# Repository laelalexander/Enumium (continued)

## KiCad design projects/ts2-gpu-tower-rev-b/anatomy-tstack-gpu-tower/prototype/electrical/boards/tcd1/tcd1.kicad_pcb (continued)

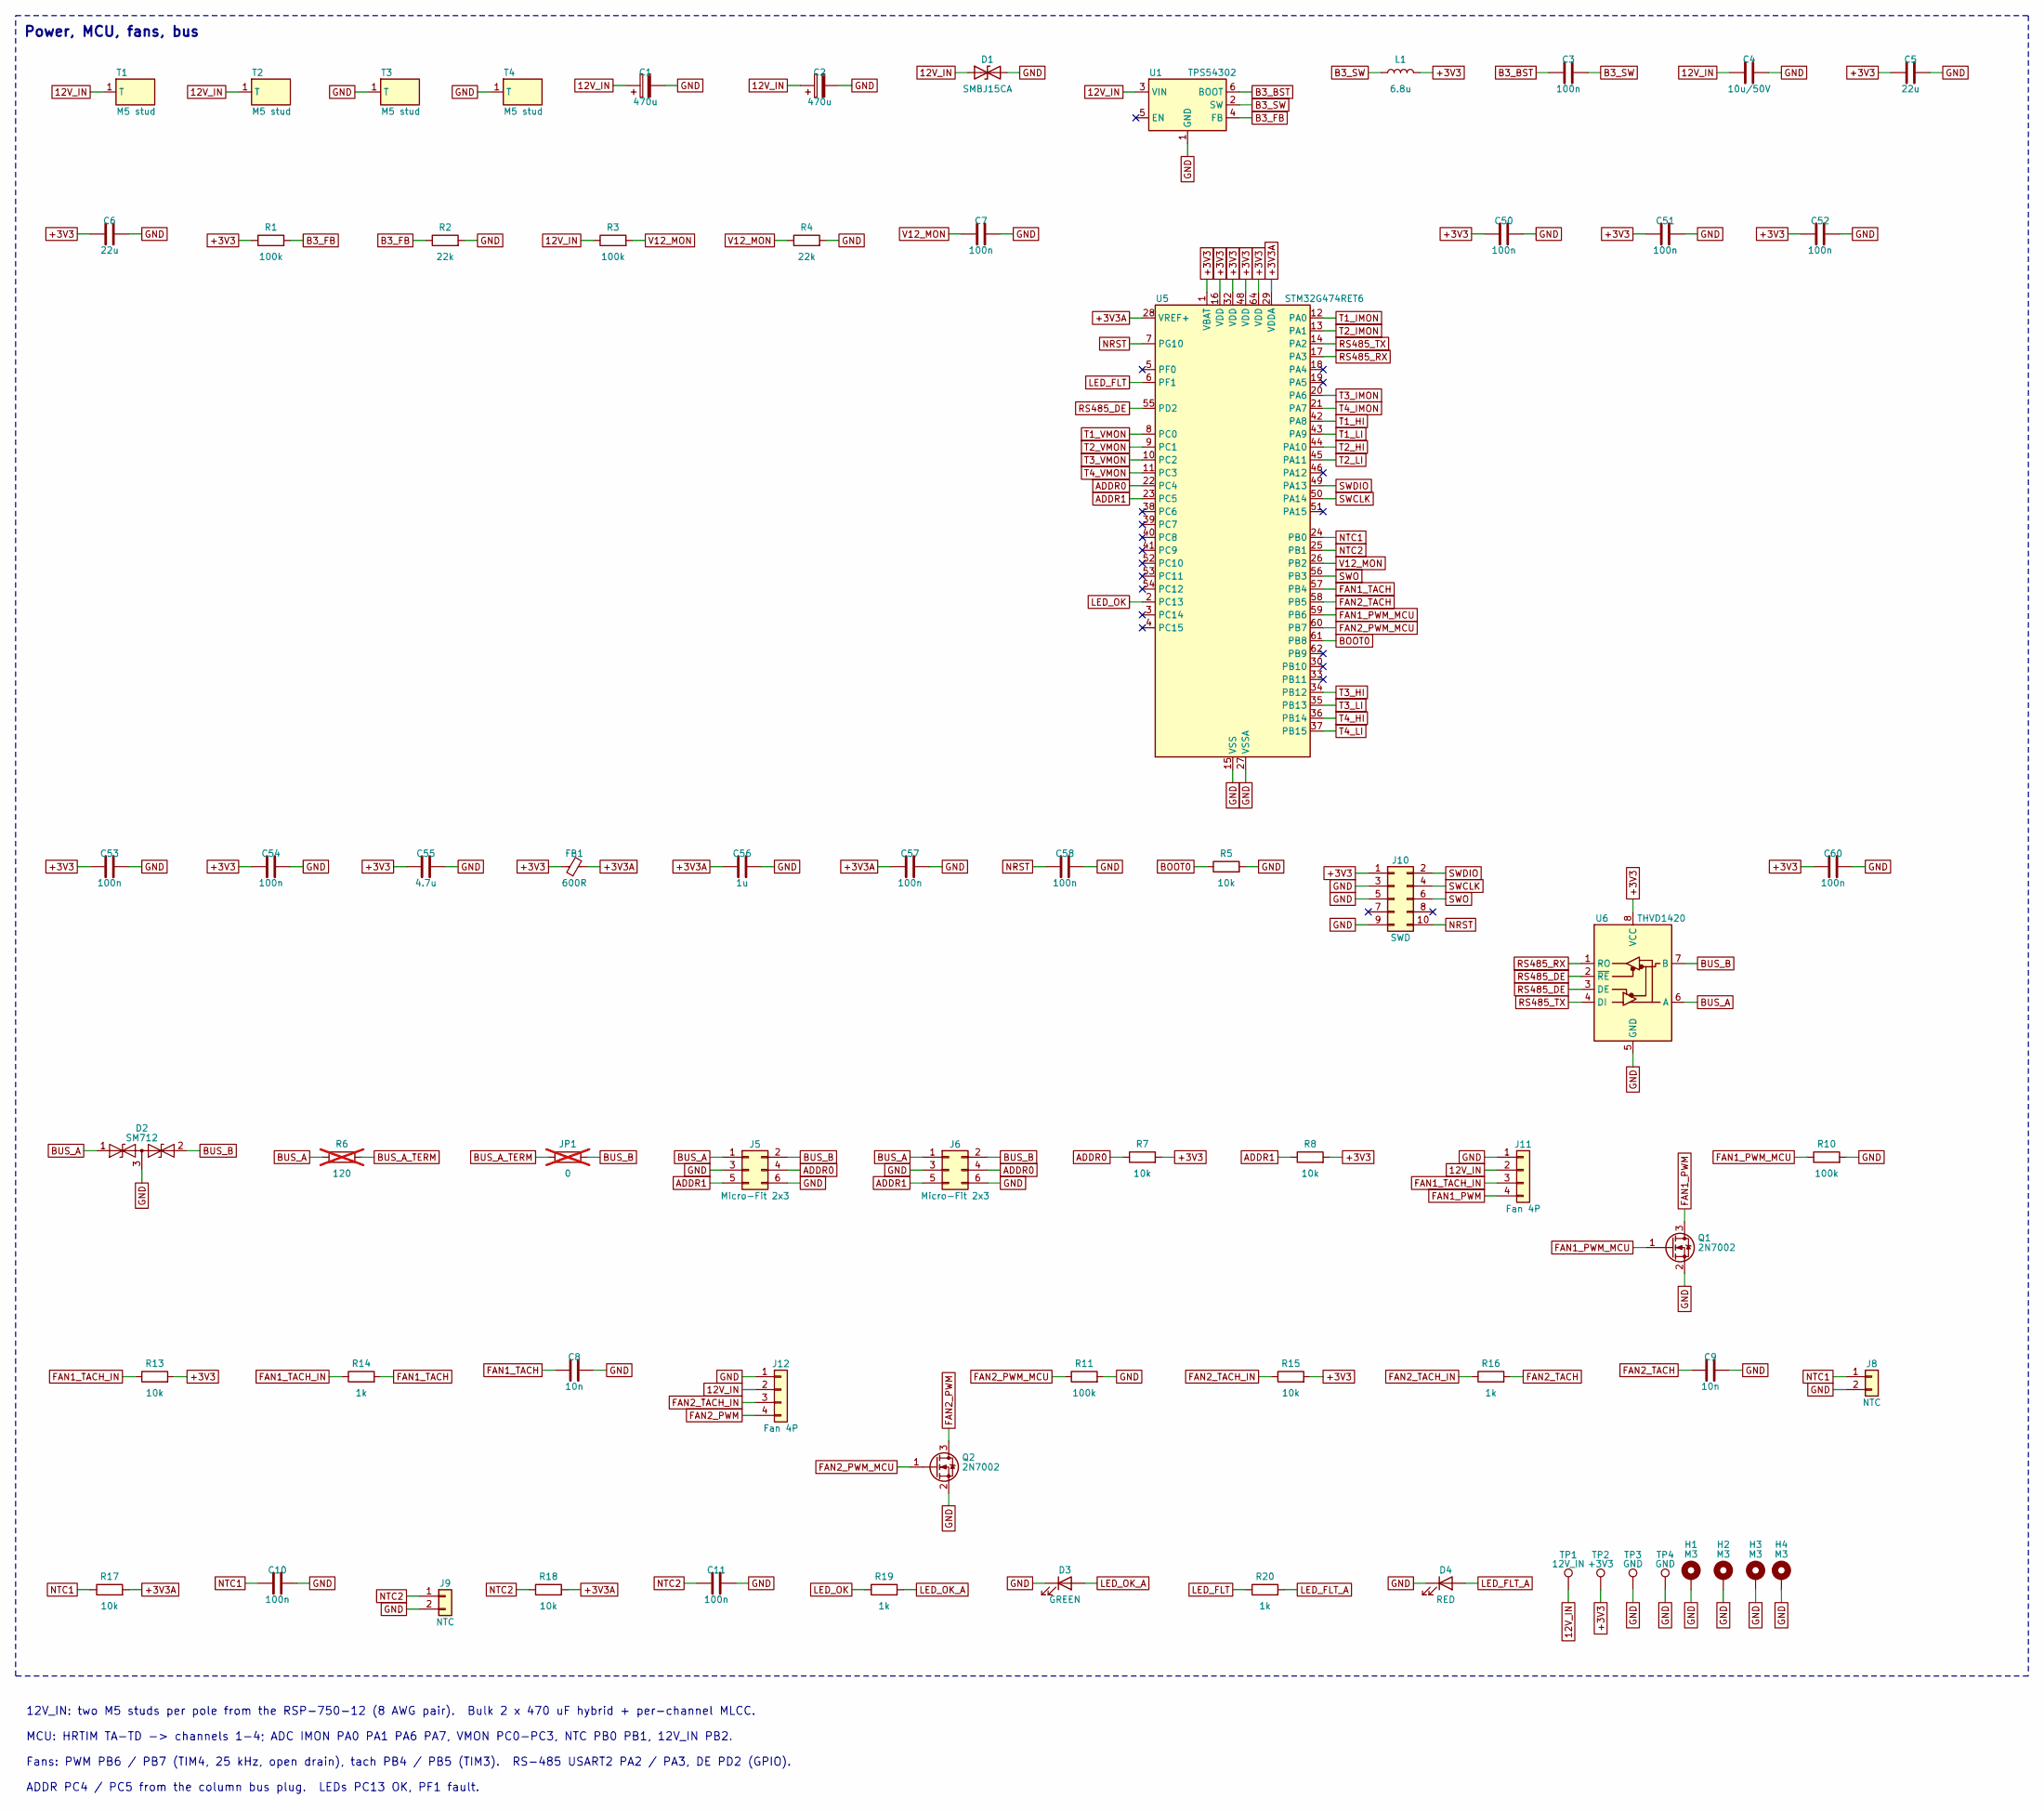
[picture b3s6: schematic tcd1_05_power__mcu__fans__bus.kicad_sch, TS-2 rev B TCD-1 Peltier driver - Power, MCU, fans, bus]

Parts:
C1, C2: 470u; CP_Elec_10x10; MPN EEH-ZA1E471P
C3, C7, C10, C11, C50, C51, C52, C53, C54, C57, C58, C60: 100n; C_0603_1608Metric; MPN CL10B104KB8NNNC; LCSC C1591
C4: 10u/50V; C_1206_3216Metric; MPN GRM31CR61H106KA12L; LCSC C13585
C5, C6: 22u; C_0805_2012Metric; MPN CL21A226MAQNNNE; LCSC C45783
C8, C9: 10n; C_0603_1608Metric; MPN CL10B103KB8NNNC; LCSC C57112
C55: 4.7u; C_0603_1608Metric; MPN CL10A475KO8NNNC; LCSC C19666
C56: 1u; C_0603_1608Metric; MPN CL10A105KA8NNNC; LCSC C15849
D1: SMBJ15CA; D_SMB; MPN SMBJ15CA
D2: SM712; SOT-23; MPN SM712.TCT
D3: GREEN; LED_0603_1608Metric; MPN 150060VS75000
D4: RED; LED_0603_1608Metric; MPN 150060RS75000
FB1: 600R; L_0603_1608Metric; MPN BLM18KG601SN1D
H1, H2, H3, H4: M3; MountingHole_3.2mm_M3_Pad_Via
J5, J6: Micro-Fit 2x3; Molex_Micro-Fit_3.0_43045-0612_2x03_P3.00mm_Vertical; MPN 43045-0612
J8, J9: NTC; JST_PH_B2B-PH-K_1x02_P2.00mm_Vertical; MPN B2B-PH-K-S
J10: SWD; PinHeader_2x05_P1.27mm_Vertical; MPN FTSH-105-01-F-DV-K
J11, J12: Fan 4P; FanPinHeader_1x04_P2.54mm_Vertical; MPN 47053-1000
JP1: 0; R_0603_1608Metric; MPN 0603WAF0000T5E; not fitted
L1: 6.8u; L_Bourns_SRP7028A_7.3x6.6mm; MPN SRP7028A-6R8M
Q1, Q2: 2N7002; SOT-23; MPN 2N7002,215
R1, R3, R10, R11: 100k; R_0603_1608Metric; MPN 0603WAF1003T5E; LCSC C25803
R2, R4: 22k; R_0603_1608Metric; MPN 0603WAF2202T5E; LCSC C31850
R5, R7, R8, R13, R15, R17, R18: 10k; R_0603_1608Metric; MPN 0603WAF1002T5E; LCSC C25804
R6: 120; R_0603_1608Metric; MPN 0603WAF1200T5E; LCSC C22787; not fitted
R14, R16, R19, R20: 1k; R_0603_1608Metric; MPN 0603WAF1001T5E; LCSC C21190
T1, T2, T3, T4: M5 stud; Power_Stud_M5_PressFit; MPN FHS-M5-15ZI [verify]
TP1: 12V_IN; TestPoint_Pad_D1.5mm
TP2: +3V3; TestPoint_Pad_D1.5mm
TP3, TP4: GND; TestPoint_Pad_D1.5mm
U1: TPS54302; SOT-23-6; MPN TPS54302DDCR
U5: STM32G474RET6; LQFP-64_10x10mm_P0.5mm; MPN STM32G474RET6
U6: THVD1420; SOIC-8_3.9x4.9mm_P1.27mm; MPN THVD1420DR

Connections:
12V_IN: C1.1, C2.1, C4.1, D1.1 (A1), J11.2, J12.2, R3.1, T1.1, T2.1, TP1.1, U1.3 (VIN); also elsewhere on the board
+3V3: C5.1, C6.1, C50.1, C51.1, C52.1, C53.1, C54.1, C55.1, C60.1, FB1.1, J10.1, L1.2, R1.1, R7.2, R8.2, R13.2, R15.2, TP2.1, U5.1 (VBAT), U5.16 (VDD), U5.32 (VDD), U5.48 (VDD), U5.64 (VDD), U6.8 (VCC); also elsewhere on the board
+3V3A: C56.1, C57.1, FB1.2, R17.2, R18.2, U5.28 (VREF+), U5.29 (VDDA)
ADDR0: J5.4, J6.4, R7.1, U5.22 (PC4)
ADDR1: J5.5, J6.5, R8.1, U5.23 (PC5)
B3_BST: C3.1, U1.6 (BOOT)
B3_FB: R1.2, R2.1, U1.4 (FB)
B3_SW: C3.2, L1.1, U1.2 (SW)
BOOT0: R5.1, U5.61 (PB8)
BUS_A: D2.1 (A1), J5.1, J6.1, R6.1, U6.6 (A)
BUS_A_TERM: JP1.1, R6.2
BUS_B: D2.2 (A2), J5.2, J6.2, JP1.2, U6.7 (B)
FAN1_PWM: J11.4, Q1.3 (D)
FAN1_PWM_MCU: Q1.1 (G), R10.1, U5.59 (PB6)
FAN1_TACH: C8.1, R14.2, U5.57 (PB4)
FAN1_TACH_IN: J11.3, R13.1, R14.1
FAN2_PWM: J12.4, Q2.3 (D)
FAN2_PWM_MCU: Q2.1 (G), R11.1, U5.60 (PB7)
FAN2_TACH: C9.1, R16.2, U5.58 (PB5)
FAN2_TACH_IN: J12.3, R15.1, R16.1
GND: C1.2, C2.2, C4.2, C5.2, C6.2, C7.2, C8.2, C9.2, C10.2, C11.2, C50.2, C51.2, C52.2, C53.2, C54.2, C55.2, C56.2, C57.2, C58.2, C60.2, D1.2 (A2), D2.3 (common), D3.1 (K), D4.1 (K), H1.1, H2.1, H3.1, H4.1, J5.3, J5.6, J6.3, J6.6, J8.2, J9.2, J10.3, J10.5, J10.9, J11.1, J12.1, Q1.2 (S), Q2.2 (S), R2.2, R4.2, R5.2, R10.2, R11.2, T3.1, T4.1, TP3.1, TP4.1, U1.1 (GND), U5.15 (VSS), U5.27 (VSSA), U5.31 (VSS), U5.47 (VSS), U5.63 (VSS), U6.5 (GND); also elsewhere on the board
LED_FLT: R20.1, U5.6 (PF1)
LED_FLT_A: D4.2 (A), R20.2
LED_OK: R19.1, U5.2 (PC13)
LED_OK_A: D3.2 (A), R19.2
NRST: C58.1, J10.10, U5.7 (PG10)
NTC1: C10.1, J8.1, R17.1, U5.24 (PB0)
NTC2: C11.1, J9.1, R18.1, U5.25 (PB1)
RS485_DE: U5.55 (PD2), U6.2 (~RE), U6.3 (DE)
RS485_RX: U5.17 (PA3), U6.1 (RO)
RS485_TX: U5.14 (PA2), U6.4 (DI)
SWCLK: J10.4, U5.50 (PA14)
SWDIO: J10.2, U5.49 (PA13)
SWO: J10.6, U5.56 (PB3)
T1_HI: U5.42 (PA8); also elsewhere on the board
T1_IMON: U5.12 (PA0); also elsewhere on the board
T1_LI: U5.43 (PA9); also elsewhere on the board
T1_VMON: U5.8 (PC0); also elsewhere on the board
T2_HI: U5.44 (PA10); also elsewhere on the board
T2_IMON: U5.13 (PA1); also elsewhere on the board
T2_LI: U5.45 (PA11); also elsewhere on the board
T2_VMON: U5.9 (PC1); also elsewhere on the board
T3_HI: U5.34 (PB12); also elsewhere on the board
T3_IMON: U5.20 (PA6); also elsewhere on the board
T3_LI: U5.35 (PB13); also elsewhere on the board
T3_VMON: U5.10 (PC2); also elsewhere on the board
T4_HI: U5.36 (PB14); also elsewhere on the board
T4_IMON: U5.21 (PA7); also elsewhere on the board
T4_LI: U5.37 (PB15); also elsewhere on the board
T4_VMON: U5.11 (PC3); also elsewhere on the board
V12_MON: C7.1, R3.2, R4.1, U5.26 (PB2)

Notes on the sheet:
Power, MCU, fans, bus
12V_IN: two M5 studs per pole from the RSP-750-12 (8 AWG pair). Bulk 2 x 470 uF hybrid + per-channel MLCC.
MCU: HRTIM TA-TD -> channels 1-4; ADC IMON PA0 PA1 PA6 PA7, VMON PC0-PC3, NTC PB0 PB1, 12V_IN PB2.
Fans: PWM PB6 / PB7 (TIM4, 25 kHz, open drain), tach PB4 / PB5 (TIM3). RS-485 USART2 PA2 / PA3, DE PD2 (GPIO).
ADDR PC4 / PC5 from the column bus plug. LEDs PC13 OK, PF1 fault.

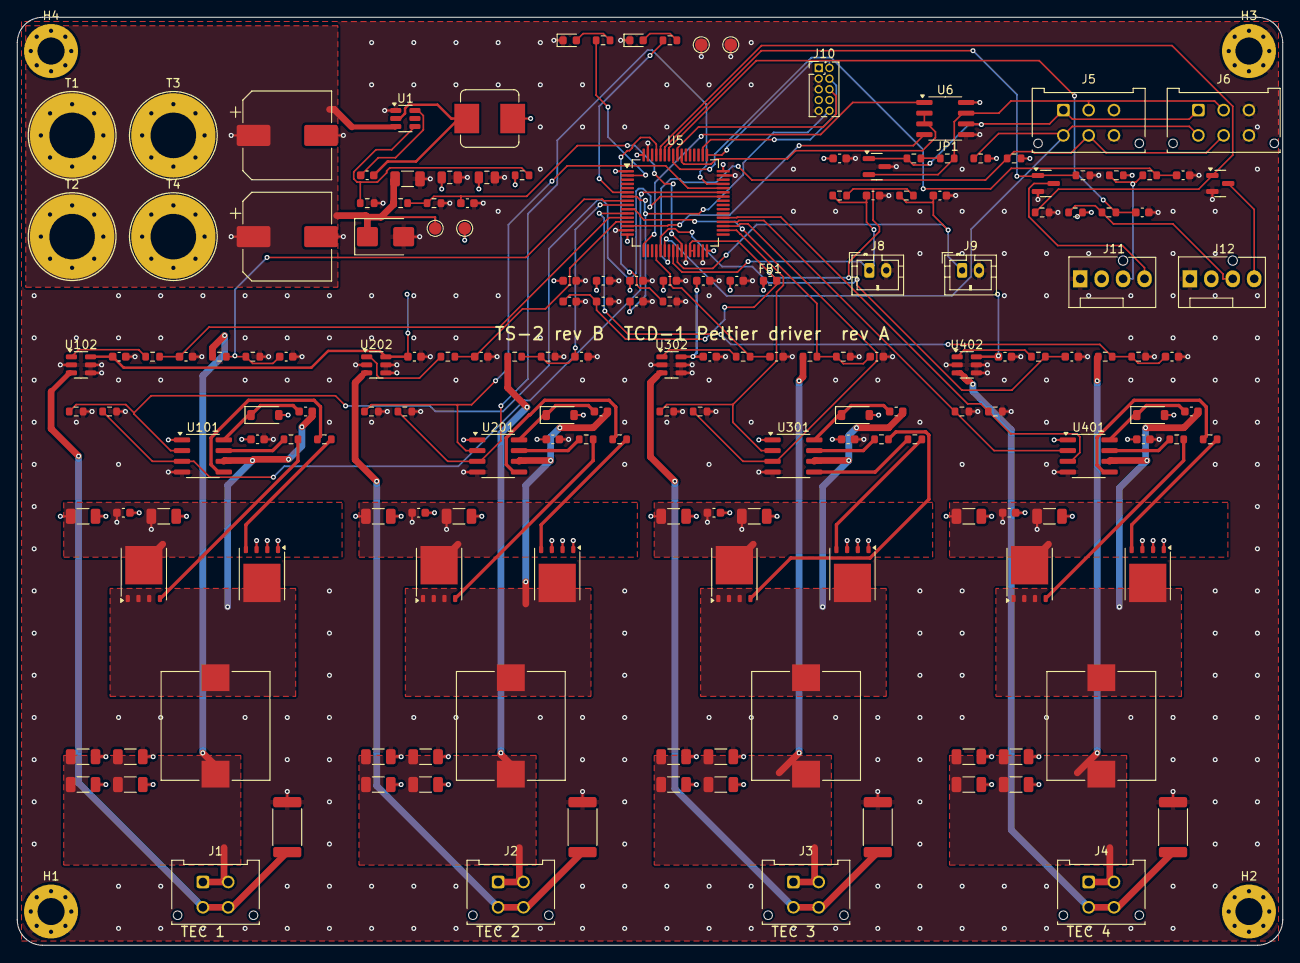
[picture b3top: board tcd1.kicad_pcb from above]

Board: 4 copper layers, 150.0 x 110.0 mm, 178 parts (0 on the bottom side), 87 nets.

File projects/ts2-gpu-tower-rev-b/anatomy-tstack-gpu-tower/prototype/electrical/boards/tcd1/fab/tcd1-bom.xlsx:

TCD1 TS-2 rev B TCD-1 Peltier driver rev A - Bill of Materials (qty per board)
Item | Qty | Designators | Value | Description | Manufacturer | MPN | Supplier PN | Footprint | Side | DNP | Unit price USD (est.) | Ext. USD (est.)
1 | 2 | C1 C2 | 470u | Hybrid polymer 470 uF 25 V 10 x 10.2 mm, 2.8 A ripple | Panasonic | EEH-ZA1E471P | PCE5003CT-ND [verify] | CP_Elec_10x10 | Top |  | 1.6 | 3.2
2 | 1 | C4 | 10u/50V | MLCC 10 uF 50 V X5R 1206 | Murata | GRM31CR61H106KA12L | LCSC C13585 | C_1206_3216Metric | Top |  | 0.06 | 0.06
3 | 2 | C5 C6 | 22u | MLCC 22 uF 25 V X5R 0805 | Samsung Electro-Mechanics | CL21A226MAQNNNE | LCSC C45783 | C_0805_2012Metric | Top |  | 0.06 | 0.12
4 | 20 | C3 C7 C10 C11 C50 C51 C52 C53 C54 C57 C58 C60 C105 C205 C305 C405 C1010 C2010 C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 | 100n | half-bridge HF loop | Samsung Electro-Mechanics | CL10B104KB8NNNC | LCSC C1591 | C_0603_1608Metric | Top |  | 0.01 | 0.2
5 | 1 | C55 | 4.7u | MLCC 4.7 uF 16 V X5R 0603 | Samsung Electro-Mechanics | CL10A475KO8NNNC | LCSC C19666 | C_0603_1608Metric | Top |  | 0.01 | 0.01
6 | 4 | C101 C201 C301 C401 | 220n | bootstrap 220 nF | Samsung Electro-Mechanics | CL10B224KO8NNNC | LCSC C21120 | C_0603_1608Metric | Top |  | 0.01 | 0.04
7 | 5 | C56 C102 C202 C302 C402 | 1u | driver VDD | Samsung Electro-Mechanics | CL10A105KA8NNNC | LCSC C15849 | C_0603_1608Metric | Top |  | 0.01 | 0.05
8 | 24 | C103 C104 C106 C107 C108 C109 C203 C204 C206 C207 C208 C209 C303 C304 C306 C307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 | 22u/25V | half-bridge input | Samsung Electro-Mechanics | CL31A226KAHNNNE | LCSC C12891 | C_1206_3216Metric | Top |  | 0.06 | 1.44
9 | 10 | C8 C9 C1011 C1012 C2011 C2012 C3011 C3012 C4011 C4012 | 10n | MLCC 10 nF 50 V X7R 0603 | Samsung Electro-Mechanics | CL10B103KB8NNNC | LCSC C57112 | C_0603_1608Metric | Top |  | 0.01 | 0.1
10 | 1 | D1 | SMBJ15CA | TVS 15 V 600 W | Littelfuse | SMBJ15CA | SMBJ15CALFCT-ND [verify] | D_SMB | Top |  | 0.3 | 0.3
11 | 1 | D2 | SM712 | RS-485 TVS -7 / +12 V asymmetric | Semtech | SM712.TCT | SM712.TCTCT-ND [verify] | SOT-23 | Top |  | 0.4 | 0.4
12 | 1 | D3 | GREEN | LED green 0603 | Wurth Elektronik | 150060VS75000 | [verify] | LED_0603_1608Metric | Top |  | 0.15 | 0.15
13 | 1 | D4 | RED | LED red 0603 | Wurth Elektronik | 150060RS75000 | [verify] | LED_0603_1608Metric | Top |  | 0.15 | 0.15
14 | 4 | D101 D201 D301 D401 | MBR0540 | Bootstrap Schottky 40 V 0.5 A | onsemi | MBR0540T1G | MBR0540T1GOSCT-ND | D_SOD-123 | Top |  | 0.1 | 0.4
15 | 1 | FB1 | 600R | Ferrite 600 ohm @ 100 MHz, VDDA / VREF+ filter | Murata | BLM18KG601SN1D | 490-5258-1-ND [verify] | L_0603_1608Metric | Top |  | 0.1 | 0.1
16 | 4 | J1 J2 J3 J4 | Micro-Fit 2x2 | TEC 1: 1/2 TEC+ (red), 3/4 TEC- (black), 18 AWG, 2 pins per pole (14 A) (mating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 | Molex | 43045-0412 | [verify] | Molex_Micro-Fit_3.0_43045-0412_2x02_P3.00mm_Vertical | Top |  | 1 | 4
17 | 2 | J5 J6 | Micro-Fit 2x3 | Column RS-485 bus: 1 A, 2 B, 3 GND, 4 ADDR0, 5 ADDR1, 6 GND (mating 43025-0600) | Molex | 43045-0612 | WM1784-ND [verify] | Molex_Micro-Fit_3.0_43045-0612_2x03_P3.00mm_Vertical | Top |  | 1.3 | 2.6
18 | 2 | J8 J9 | NTC | NTC 10k B3950 cable sensor: TEC hot side, tower 1 | JST | B2B-PH-K-S | 455-1704-ND | JST_PH_B2B-PH-K_1x02_P2.00mm_Vertical | Top |  | 0.2 | 0.4
19 | 1 | J10 | SWD | Arm Cortex debug 10-pin 1.27 mm (SWD + SWO), keyed | Samtec | FTSH-105-01-F-DV-K | SAM8796-ND [verify] | PinHeader_2x05_P1.27mm_Vertical | Top |  | 2.1 | 2.1
20 | 2 | J11 J12 | Fan 4P | Heat-pipe tower fan 1, 4-pin PWM (Intel fan spec): 1 GND, 2 +12 V, 3 tach, 4 PWM | Molex | 47053-1000 | WM4330-ND [verify] | FanPinHeader_1x04_P2.54mm_Vertical | Top |  | 0.4 | 0.8
21 | 1 | JP1 | 0 | Termination link (fit with R6 on the end node) | UNI-ROYAL | 0603WAF0000T5E |  | R_0603_1608Metric | Top | DNP | 0 | 0
22 | 1 | L1 | 6.8u | Inductor 6.8 uH shielded 7.3 x 6.6 x 2.8 mm | Bourns | SRP7028A-6R8M | SRP7028A-6R8MCT-ND [verify] | L_Bourns_SRP7028A_7.3x6.6mm | Top |  | 0.6 | 0.6
23 | 4 | L101 L201 L301 L401 | 6.8u | Power inductor 6.8 uH ~ 20 A sat, 12.9 x 12.9 mm | Vishay Dale | IHLP5050FDER6R8M01 | 541-1242-1-ND [verify] | L_Vishay_IHLP-5050 | Top |  | 2.2 | 8.800000000000001
24 | 2 | Q1 Q2 | 2N7002 | N-MOSFET 60 V 0.3 A SOT-23, fan PWM open drain | Nexperia | 2N7002,215 | 1727-2N7002215CT-ND | SOT-23 | Top |  | 0.05 | 0.1
25 | 4 | Q101 Q201 Q301 Q401 | CSD17578Q5A | N-MOSFET 30 V SON 5x6, high side (low Qg) | Texas Instruments | CSD17578Q5A | 296-37934-1-ND [verify] | TDSON-8-1 | Top |  | 0.6 | 2.4
26 | 4 | Q102 Q202 Q302 Q402 | CSD17556Q5B | N-MOSFET 30 V 1.4 mOhm SON 5x6, low side (synchronous rectifier) | Texas Instruments | CSD17556Q5B | 296-37919-1-ND [verify] | TDSON-8-1 | Top |  | 1.4 | 5.6
27 | 16 | R1 R3 R10 R11 R103 R104 R107 R203 R204 R207 R303 R304 R307 R403 R404 R407 | 100k | HI pull-down (off in reset) | UNI-ROYAL | 0603WAF1003T5E | LCSC C25803 | R_0603_1608Metric | Top |  | 0.002 | 0.03
28 | 1 | R6 | 120 | Bus termination 120 ohm - fit on the end node only | UNI-ROYAL | 0603WAF1200T5E | LCSC C22787 | R_0603_1608Metric | Top | DNP | 0.002 | 0
29 | 7 | R5 R7 R8 R13 R15 R17 R18 | 10k | BOOT0 pull-down (boot from flash) | UNI-ROYAL | 0603WAF1002T5E | LCSC C25804 | R_0603_1608Metric | Top |  | 0.002 | 0.01
30 | 8 | R101 R102 R201 R202 R301 R302 R401 R402 | 10 | high-side gate 10 ohm | UNI-ROYAL | 0603WAF100JT5E | LCSC C22859 | R_0603_1608Metric | Top |  | 0.002 | 0.02
31 | 4 | R105 R205 R305 R405 | 2m | Shunt 2 mOhm 1 % 2512 1 W (TEC return) | Vishay Dale | WSL2512R0020FEA | WSL2512.002FCT-ND [verify] | R_2512_6332Metric | Top |  | 0.7 | 2.8
32 | 8 | R14 R16 R19 R20 R106 R206 R306 R406 | 1k | ADC RC | UNI-ROYAL | 0603WAF1001T5E | LCSC C21190 | R_0603_1608Metric | Top |  | 0.002 | 0.02
33 | 6 | R2 R4 R108 R208 R308 R408 | 22k | VOUT divider bottom | UNI-ROYAL | 0603WAF2202T5E | LCSC C31850 | R_0603_1608Metric | Top |  | 0.002 | 0.01
34 | 4 | T1 T2 T3 T4 | M5 stud | M5 press-fit stud, +12 V from the RSP-750-12 (ring lug, 3 N m) | PennEngineering | FHS-M5-15ZI [verify] | [verify] | Power_Stud_M5_PressFit | Top |  | 0.7 | 2.8
35 | 1 | U1 | TPS54302 | 3.3 V 3 A buck | Texas Instruments | TPS54302DDCR | 296-47648-1-ND [verify] | SOT-23-6 | Top |  | 0.8 | 0.8
36 | 1 | U5 | STM32G474RET6 | MCU Arm Cortex-M4F 170 MHz, 512 KB flash, LQFP-64 (pin map from the KiCad STM32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 | STMicroelectronics | STM32G474RET6 | 497-19525-ND [verify] | LQFP-64_10x10mm_P0.5mm | Top |  | 7.9 | 7.9
37 | 1 | U6 | THVD1420 | RS-485 half duplex 12 Mbps, 3.3 V, +/-12 kV ESD, fail-safe receiver | Texas Instruments | THVD1420DR | 296-THVD1420DRCT-ND [verify] | SOIC-8_3.9x4.9mm_P1.27mm | Top |  | 1.6 | 1.6
38 | 4 | U101 U201 U301 U401 | LM5109B | Half-bridge gate driver 100 V 1 A, independent HI / LI inputs | Texas Instruments | LM5109BMAX/NOPB | LM5109BMAX/NOPBCT-ND [verify] | SOIC-8_3.9x4.9mm_P1.27mm | Top |  | 1.3 | 5.2
39 | 4 | U102 U202 U302 U402 | INA181A2 | Current-sense amplifier gain 50 (0.1 V/A) | Texas Instruments | INA181A2IDBVR | 296-49601-1-ND [verify] | SOT-23-6 | Top |  | 0.9 | 3.6
 |  |  |  | Estimated parts cost per board (excl. DNP, before price breaks) |  |  |  |  |  |  |  | 58.91
